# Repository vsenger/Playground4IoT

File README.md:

# Playground4IoT

*"There are three states of being: Not knowing, action and completion"*
Cult of Done Manifesto, Bre Pettis

Welcome Playgrounder to our repository where you can find libraries, firmwares, Arduino Sketch, tutorials and more for Playground4IoT development board. Playground4IoT is a development board that make easy and fun to start playing, prototyping and deploying connected devices projects using AWS Services like AWS IoT Core and Amazon FreeRTOS with security for adults, deployment over-the-air and management of big fleets of devices in production.

This project was done by AWS Developer Relations Team but is open-source, don't hesitate to clone it, produce, have fun, make money, change the world or anything else you dream. Developer Relations Team exist to help you to make it happen, count on us.. ALWAYS!

## Technical Resume

*"Accept that everything is a draft. It helps to get it done."*
The Cult of Done Manifesto, Bre Pettis

This board is based on ESP32, a powerful SoC that can run in low-energy with solar panel and simple battery forever and you can program using Arduino IDE, libraries and frameworks or you can go deeper and programa with Amazon FreeRTOS for industry ready devices.

* Based on ESP32 SoC (System-on-chip) with WIFI and Bluetooth
* Accelerometer Sensor
* Temperature, Humidity and Pressure sensor
* Light sensor
* Battery voltage sensor
* Solar panel sensor
* Groovy connectors
* External Solar Panel Connector
* External Battery Connector
* Battery charger system (cable / solar panel)
* And a lot of love!

## Let's Play!

*"People without dirty hands are wrong, doing something makes you right!"*
The Cult of Done Manifesto, Bre Pettis

Here we have a simple description image showing the main parts:

1. Power on / off
2. IoT Button: you can use as IoT button or anything else!
3. The loooovely OLED display: you can code turn on and off to save energy, sure thing!
4. ESP32: the core! and it's compatible with Amazon FreeRTOS and very cheap
5. GPIO: the place you can extend in a "maker way"
6. Reset Button
7. Solar panel connector: yesss! I can survive with Sun, at least in Brazil ahahah
8. External Battery Connector
9. USB C: you can use to charge the battery (nice!!!), to upload firmware hard-wire (but you can do it over-the-air!) or to debug your board
10. USB to Serial Controller: this is the CH340 chip, you may need or not to install a driver for it
11. You will find three additional connectors under the board and they are Grove compatible, so you can plug [200+ different sensors](https://www.seeedstudio.com/catalogsearch/result/index/?cat=890&q=grove).

To start playing with this device (or toy?!?) we have those main steps:
1. Install Playground4IoT usb driver
1. Install and setup Arduino IDE environment: install Arduino IDE itself and setup for E	SP32 development 
1. Install Arduino libraries for the Playground4IoT sensors
1. Create a thing to represent your board in AWS IoT Core
1. Setup the wifi credential, root-ca, device certificate and private key inside the Arduino C code
1. Upload the Arduino code to your board using an USB cable
1. Open AWS IoT Core console and start playing with your board

Now let's go deep in each step!

## 1. Install Playground4IoT usb driver

Our board uses a chip called CH340 to communicate throught the USB-C port, this chip is actualy a Serial - USB converter so once you have the driver installed you will see the Playground4IoT as a Serial port (windows: COM1, COM7, COMx - linux /dev/acm0 /dev/usb0 - macs /dev/cu.wchusbserial). 

> **_NOTE:_**  MacOS Mojave (and newer) already includes a CH34x driver from Apple. Do not install other versions as it may cause issues. Read more on https://github.com/adrianmihalko/ch340g-ch34g-ch34x-mac-os-x-driver/pull/19.

Follow this nice sparkfun.com tutorial to install the driver: https://learn.sparkfun.com/tutorials/how-to-install-ch340-drivers/all

## 2. Arduino IDE

We have different ways to start programming our Playground4IoT that is based on ESP32 SoC and the simple way to do it is using Arduino IDE. It's a very popular IDE / tool for writing firmwares they call sketches using a simplified C sintax with many libraries to abstract all the hardware and C complex code.

To install Arduino IDE go to Arduino Web Site, download and install it, it's quite simlpe. Here is the link: https://www.arduino.cc/en/Main/Software

After installing the Arduino IDE we must add the ESP32 support. 

1) Open your Arduino IDE

2) Go to File -> Preferences

3) Enter https://dl.espressif.com/dl/package_esp32_index.json into the “Additional Board Manager URLs” field as shown in the figure below. Then, click the “OK” button:

4) Open the Boards Manager. Go to Tools > Board > Boards Manager…

5) Search for ESP32 and press install button for the “ESP32 by Espressif Systems“:

Now wait until it finish the downlaod and install

All done with ESP32 support for Arduino IDE:

6) Choose the "ESP32 Dev Module" in boards manager:

7) Now it's time to find your USB port, don't plug your board in your computer and check which ports you have on the Tools -> Port menu:

8) Now plug your Playground4IoT and check this menu again, you should see something new like here that COM7 is the choosen port:

## 3. Install Arduino Libraries for our Sensors

The Playground for IoT uses some sensors that has specific C libraries to make it easy to use. All we need to do is copy the folders in /Playground4IoT/Arduino/Libraries to your $HOME/Documents/Arduino/Library.

## 4. AWS IoT Core Setup

1) Now we need to setup the cloud side of the moon... We will create a thing to represent our Playground4IoT board and also the certificate and security keys. Open your AWS IoT Core Console and click Manage -> Things -> Register a single AWS IoT thing:

2) Let's choose "Create a single thing"

3) Now give a name to your thing and click next

4) Now choose "One-click certificate creation"

5) You can finally download your thing's certificate and private key

6) Click Activate to make your certicates valid

7) Download ROOT Certificate Authority clicking in "A root CA for AWS IoT Download" (this opens the AWS documentation and you'll need to choose one of the CAs on the page)

8) You will be redirected to another page that you can choose some options:

9) Now we need to take note of our AWS IoT Core endpoint to use in the next step. Open AWS IoT Core Console and click settings

10) We need to create a policy for our device, click Policies -> Create

11) Give a name and choose action iot:* and replace topic name with * (just for testing proposal, the policy for real projects should be restrictive!). Choose Effect Allow and click Create

12) Now let's associate the policy with the Thing Certificate, to do this click in the IoT Thing you've created, click Security and then click in the Certificate:

13) Click Policies

14) Click Actions menu -> Attach Policy

15) Choose the created Policy and click Attach:

Ufff, done!

## 5. Let's code!

1) Clone Playground4IoT repo: git clone https://github.com/vsenger/Playground4IoT

2) Open your Arduino IDE and make sure you selected the right USB port and ESP32 board!

3) Open the Arduino Sketch with current the firmware located inside the folder you clone the github repo: Playground4IoT/arduino/Playground4IoTFirmware-V0/

4) Setup your SSID and password: scroll down to the line around 60 and change:

1. The host name to your AWS IoT Core Thing name
2. SSID and passsword
3. Optional: change the name of the topics we are going to use to communicate with our board 

5) Let's configure our credentials: click in secrets.h tab and then update:

1. AWS IoT Core endpoint
2. ROOT CA certificate: open the downloaded file and copy and paste the content
3. Same things for Device Certificate and Private Key. 

## 6. Upload and fingers crossed

Now click the Upload button and wait until it compile and upload to your board. Keep your eyes in the log message panel, it's "normal" to have warning messages :).

## 7. Let's Play! 

Time to have fun! Open your AWS IoT Core Console and click Test

Type playground/sensors and click Subscribe

Type playground/sensors and click Subscribe

Now you should start seeing the json results!

## 8. Oppss, not working and now?

Chime Vini vsenger@ is now the first option but you can check the following:

1. Is your USB port ok?
2. Did you get any error message during the compile and upload process?
3. Did you choose the right Arduino Board setting to ESP32 Dev?
4. Can you open the Arduino Serial monitor?

## 9. More to come!

From here you can start changing the Arduino code to improve anything you want or do some local logic implementation reacting locally based on sensors data.

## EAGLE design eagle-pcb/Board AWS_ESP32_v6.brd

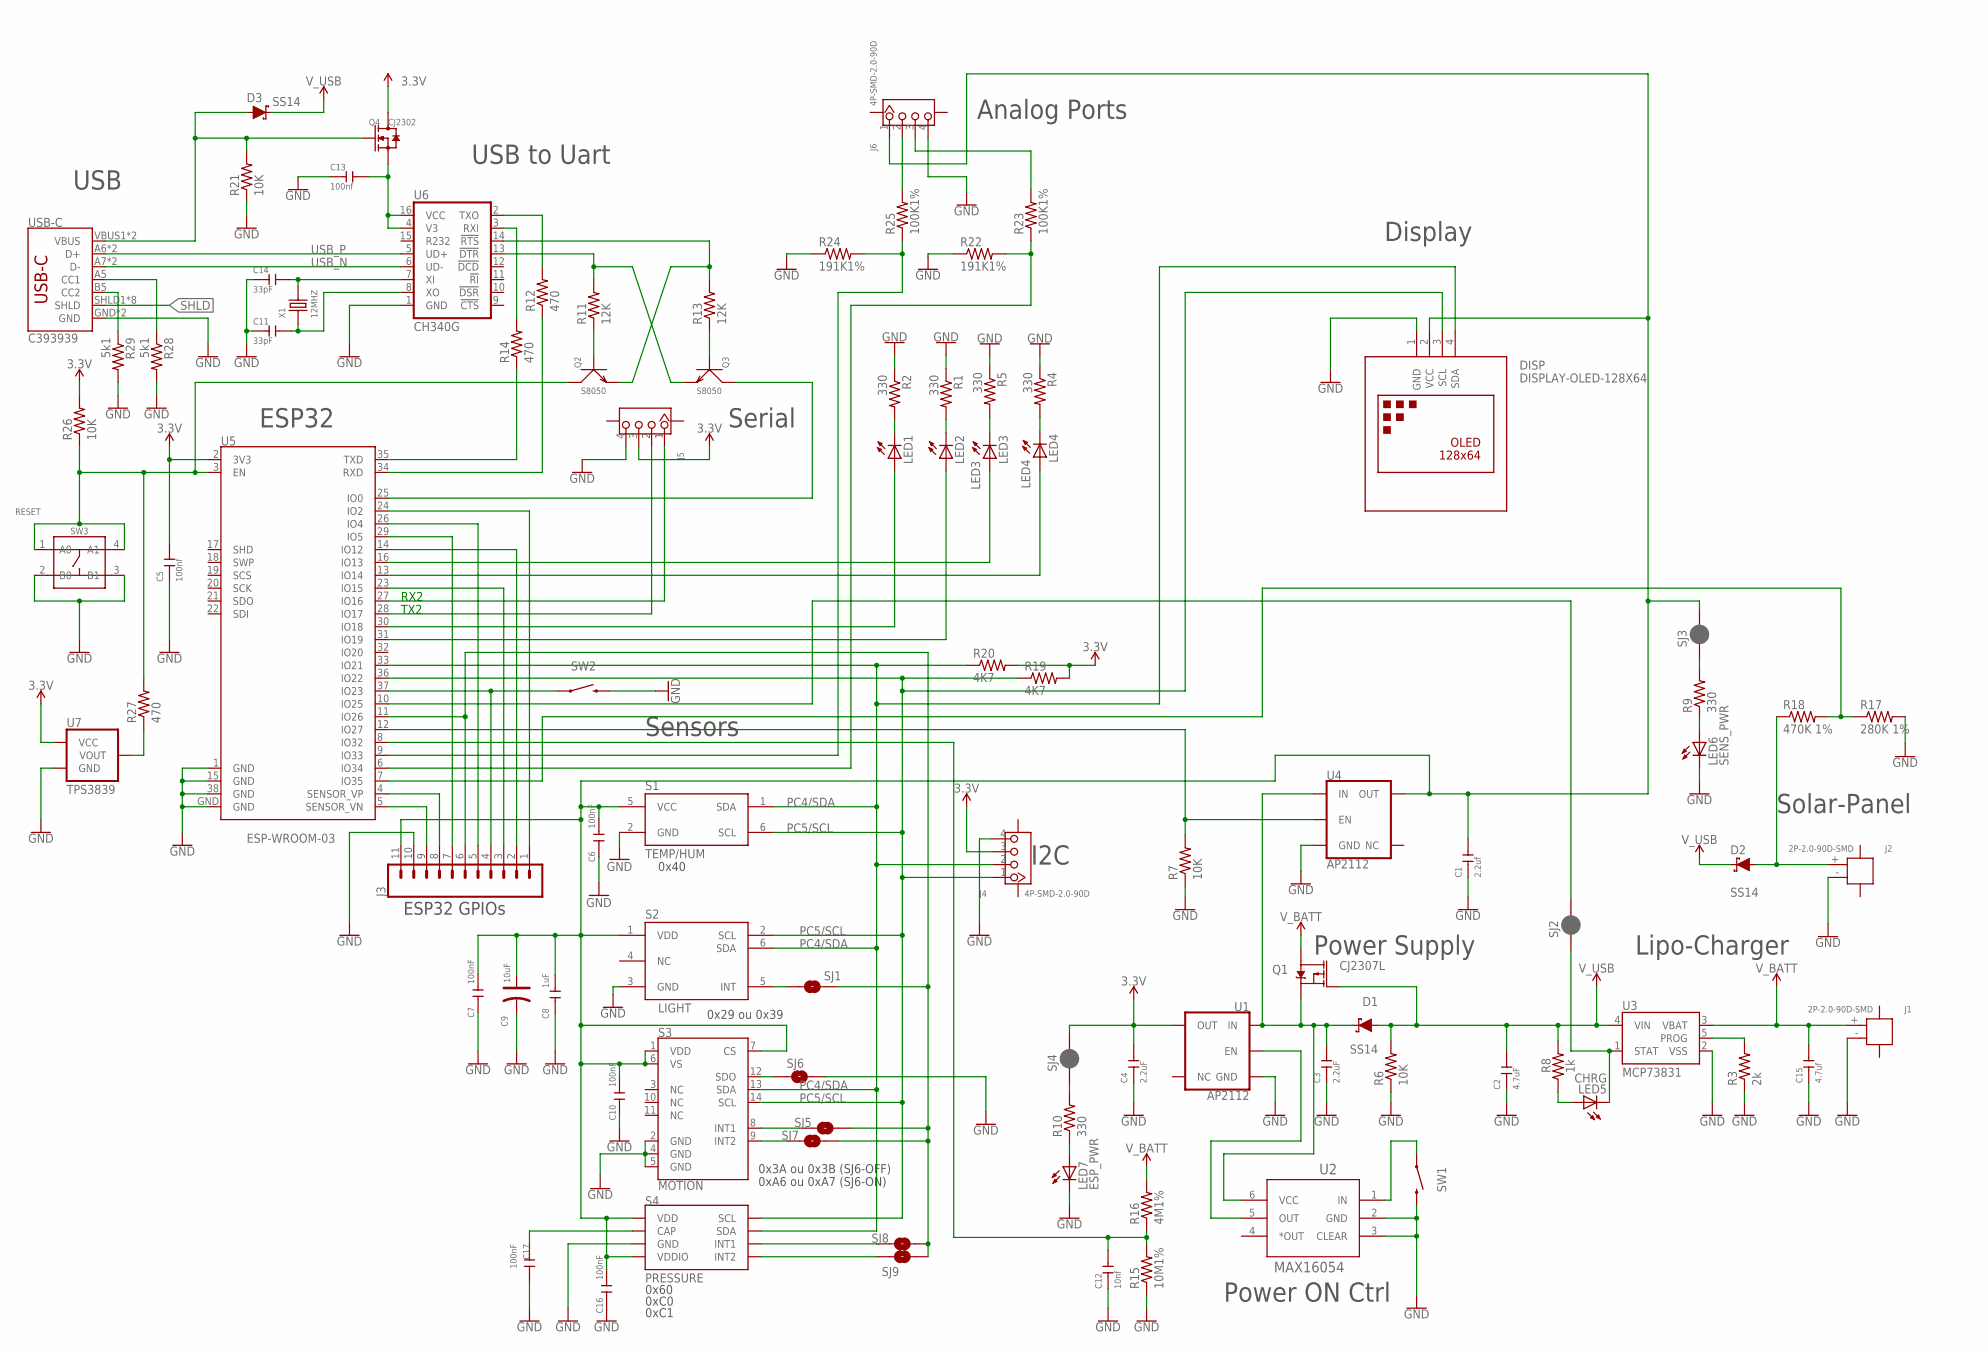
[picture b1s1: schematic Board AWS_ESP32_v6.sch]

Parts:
C1: 2.2uf; C0603
C2: 4.7uF; C0603
C3, C4: 2.2uF; C0603
C5, C13: 100nf; C0603
C6, C7, C10, C16, C17: 100nF; C0603
C8: 1uF; C0805
C9: 10uF; AVX-A
C11, C14: 33pF; C0603
C12: 10nf; C0603
C15: 4.7uf; C0603
D1, D2, D3: SS14; SMA-DIODE
DISP: DISPLAY-OLED-128X64; DISPLAY-OLED-128X64-I2C
J1, J2: 2P-2.0-90D-SMD; HW2-SMD-2.0-90D
J3: CONN_11; 1X11
J4, J5, J6: 4P-SMD-2.0-90D; HW4-SMD-2.0-90D
LED1: LED1; LED-0603
LED2: LED2; LED-0603
LED3: LED3; LED-0603
LED4: LED4; LED-0603
LED5: CHRG; LED-0603
LED6: SENS_PWR; LED-0603
LED7: ESP_PWR; LED-0603
Q1: CJ2307L; SOT23-3
Q2, Q3: S8050; SOT-23
Q4: CJ2302; SOT-23
R1, R2, R4, R5, R9, R10: 330; 0805
R3: 2k; 0805
R6, R7, R21, R26: 10K; 0805
R8: 1k; 0805
R11, R13: 12K; 0805
R12, R14, R27: 470; 0805
R15: 10M1%; 0805
R16: 4M1%; 0805
R17: 280K 1%; 0805
R18: 470K 1%; 0805
R19, R20: 4K7; 0805
R22, R24: 191K1%; 0805
R23, R25: 100K1%; 0805
R28, R29: 5k1; 0805
S1: TEMP/HUM; WSON6
S2: LIGHT; FN-6
S3: MOTION; LGA-14
S4: PRESSURE; LGA8
SJ1: IRQ_LIGHT; SJ_2S-NO
SJ2, SJ3, SJ4: JUMPER-SMT_2_NC_PASTE_SILK; SMT-JUMPER_2_NC_PASTE_SILK
SJ5, SJ7, SJ8: INT1; SJ_2S-NO
SJ6: ADXL_ADDRESS; SJ_2S-NO
SJ9: INT2; SJ_2S-NO
SW1, SW2: MOMENTARY-SWITCH-SPST-SMD-6.0X3.5MM; TACTILE_SWITCH_SMD_6.0X3.5MM
SW3: RESET; SW4-SMD-6.0X6.0X5.0MM
U1, U4: AP2112; SOT23-5
U2: MAX16054; SOT23-6
U3: MCP73831; SOT23-5
U5: ESP-WROOM-03
U6: CH340G; SO016
U7: TPS3839; SOT23-3
USB-C: C393939; SPARKFUN-CONNECTORS_USB-C-16P
X1: 12MHZ; X2-SMD-5.0X3.2X1.3MM

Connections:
3.3V: C4.2, C5.2, J4.3, J5.3, Q4.3 (D), R19.2, R20.2, R26.2, SJ4.2, U1.5 (OUT), U5.2 (3V3), U7.3 (VCC)
BEE_RESET: Q2.3 (C), R26.1, R27.2, SW3.1 (A0), SW3.4 (A1), U5.3 (EN)
GND: C1.1, C2.1, C3.1, C4.1, C5.1, C6.1, C7.1, C8.2, C9.-, C10.1, C11.1, C12.1, C13.1, C14.1, C15.1, C16.1, C17.2, DISP.1 (GND), J1.- (2), J2.- (2), J3.10, J4.4, J5.4, J6.4, LED6.C, LED7.C, R1.1, R2.1, R3.1, R4.1, R5.1, R6.1, R7.1, R15.1, R17.2, R21.1, R22.1, R24.1, R28.2, R29.2, S1.2 (GND), S2.3 (GND), S3.2 (GND), S3.4 (GND), S3.5 (GND), S4.3 (GND), SJ6.2, SW1.2, SW2.2, SW3.2 (B0), SW3.3 (B1), U1.2 (GND), U2.2 (GND), U2.3 (CLEAR), U3.2 (VSS), U4.2 (GND), U5.1 (GND), U5.15 (GND), U5.38 (GND), U5.GND, U6.1 (GND), U7.1 (GND), USB-C.GND, USB-C.GND2 (GND)
unnamed: C1.2, C6.2, C7.2, C8.1, C9.+, C10.2, C16.2, DISP.2 (VCC), J3.11, J6.1, S1.5 (VCC), S2.1 (VDD), S3.1 (VDD), S3.6 (VS), S3.7 (CS), S4.1 (VDD), S4.4 (VDDIO), SJ3.2, U4.5 (OUT)
unnamed: LED3.A, U5.16 (IO13)
unnamed: D2.A, J2.+ (1), R18.1
unnamed: R27.1, U7.2 (VOUT)
unnamed: LED1.A, U5.30 (IO18)
unnamed: J3.5, U5.26 (IO4)
unnamed: C17.1, S4.2 (CAP)
unnamed: S3.8 (INT1), SJ5.1
unnamed: S3.9 (INT2), SJ7.1
unnamed: C13.2, Q4.2 (S), U6.4 (V3), U6.16 (VCC)
unnamed: LED2.A, U5.31 (IO19)
unnamed: C12.2, R15.2, R16.1, U5.8 (IO32)
unnamed: J3.4, SW2.1, U5.37 (IO23)
unnamed: SW1.1, U2.1 (IN)
unnamed: C14.2, U6.7 (XI), X1.2
unnamed: J5.1, U5.27 (IO16)
unnamed: J5.2, U5.28 (IO17)
unnamed: U1.3 (EN), U2.5 (OUT)
unnamed: Q2.1 (B), R11.1
unnamed: C11.2, U6.8 (XO), X1.1
unnamed: S3.12 (SDO), SJ6.1
unnamed: R3.2, U3.5 (PROG)
unnamed: D3.A, Q4.1 (G), R21.2, USB-C.VBUS1 (VBUS), USB-C.VBUS2 (VBUS)
unnamed: R29.1, USB-C.B5 (CC2)
unnamed: S4.6 (INT1), SJ8.1
unnamed: S4.5 (INT2), SJ9.1
unnamed: S2.5 (INT), SJ1.1
unnamed: R12.1, U5.34 (RXD)
unnamed: R14.1, U5.35 (TXD)
unnamed: Q3.1 (B), R13.1
unnamed: R28.1, USB-C.A5 (CC1)
unnamed: LED1.C, R2.2
unnamed: LED2.C, R1.2
unnamed: Q2.2 (E), R13.2, U6.14 (!RTS)
unnamed: LED4.C, R4.2
unnamed: LED3.C, R5.2
unnamed: Q3.3 (C), U5.25 (IO0)
unnamed: Q3.2 (E), R11.2, U6.13 (!DTR)
unnamed: R24.2, R25.1, U5.9 (IO33)
unnamed: R22.2, R23.1, U5.6 (IO34)
unnamed: J6.2, R25.2
unnamed: J6.3, R23.2
unnamed: R17.1, R18.2, U5.7 (IO35)
unnamed: R14.2, U6.3 (RXI)
unnamed: R12.2, U6.2 (TXO)
unnamed: SJ2.2, U5.10 (IO25)
unnamed: J3.7, U5.29 (IO5)
unnamed: LED5.A, R8.1
unnamed: C3.2, D1.C, Q1.2 (S), U1.1 (IN), U2.6 (VCC), U4.1 (IN)
unnamed: LED7.A, R10.1
unnamed: R10.2, SJ4.1
unnamed: LED5.C, SJ2.1, U3.1 (STAT)
unnamed: LED4.A, U5.13 (IO14)
unnamed: LED6.A, R9.1
unnamed: R7.2, U4.3 (EN), U5.12 (IO27)
unnamed: R9.2, SJ3.1
unnamed: J3.9, U5.5 (SENSOR_VN)
unnamed: J3.8, U5.4 (SENSOR_VP)
unnamed: J3.3, U5.23 (IO15)
unnamed: J3.2, U5.14 (IO12)
unnamed: J3.1, U5.24 (IO2)
PC4/SDA: DISP.4 (SDA), J4.2, R20.1, S1.1 (SDA), S2.6 (SDA), S3.13 (SDA), S4.7 (SDA), U5.33 (IO21)
PC5/SCL: DISP.3 (SCL), J4.1, R19.1, S1.6 (SCL), S2.2 (SCL), S3.14 (SCL), S4.8 (SCL), U5.36 (IO22)
PD3/IRQ: J3.6, SJ1.2, SJ5.2, SJ7.2, SJ8.2, SJ9.2, U5.11 (IO26)
SHLD: USB-C.SHLD1 (SHLD), USB-C.SHLD2 (SHLD), USB-C.SHLD3 (SHLD), USB-C.SHLD4 (SHLD), USB-C.SHLD5 (SHLD), USB-C.SHLD6 (SHLD), USB-C.SHLD7 (SHLD), USB-C.SHLD8 (SHLD)
USB_N: U6.6 (UD-), USB-C.A7 (D-), USB-C.B7 (D-)
USB_P: U6.5 (UD+), USB-C.A6 (D+), USB-C.B6 (D+)
V_BATT: C15.2, J1.+ (1), Q1.3 (D), R16.2, U3.3 (VBAT)
V_USB: C2.2, D1.A, D2.C, D3.C, Q1.1 (G), R6.2, R8.2, U3.4 (VIN)

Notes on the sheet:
USB
I2C
Sensors
0x60
0xC1
0xC0
0x29 ou 0x39
0x40
Serial
ESP32
Power Supply
USB to Uart
Analog Ports
Lipo-Charger
ESP32 GPIOs
RX2
TX2
Solar-Panel
Display
0x3A ou 0x3B (SJ6-OFF)
0xA6 ou 0xA7 (SJ6-ON)
Power ON Ctrl

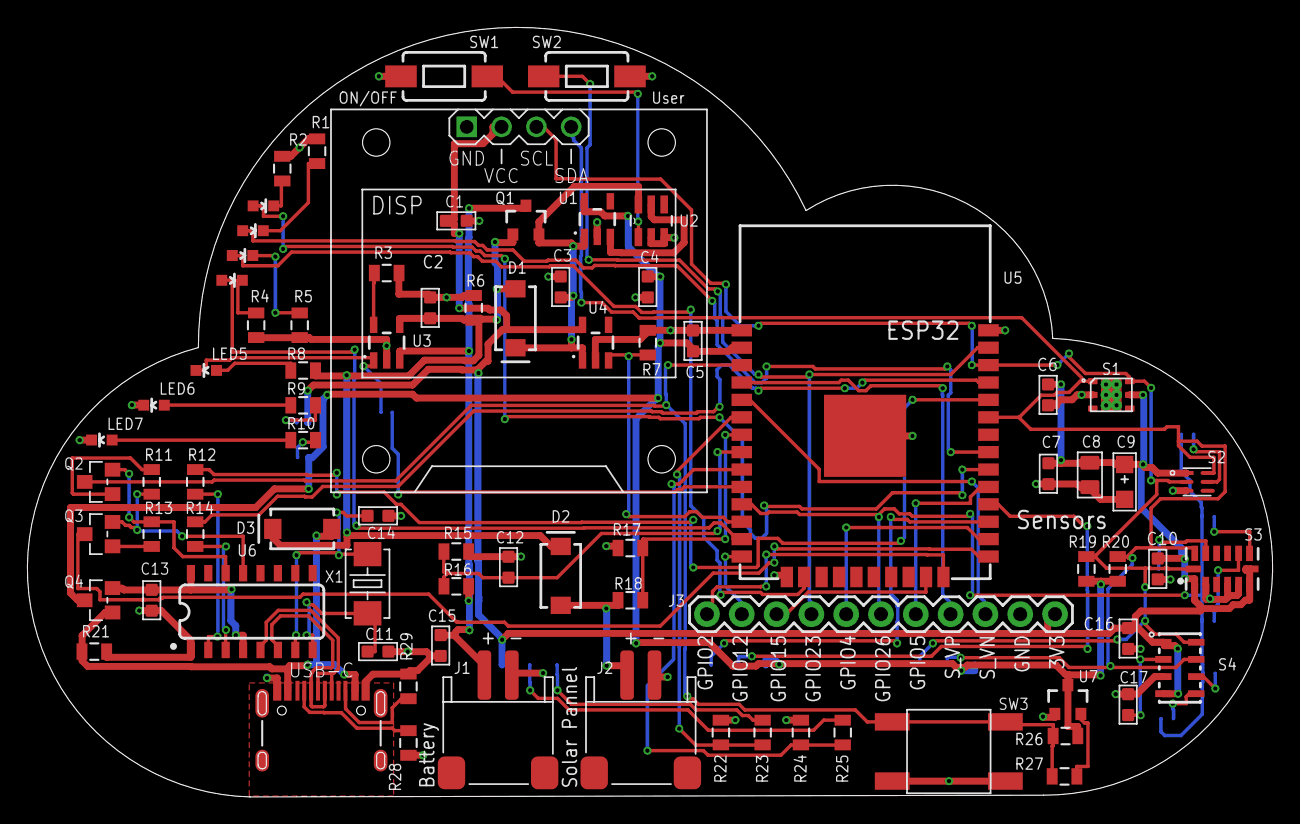
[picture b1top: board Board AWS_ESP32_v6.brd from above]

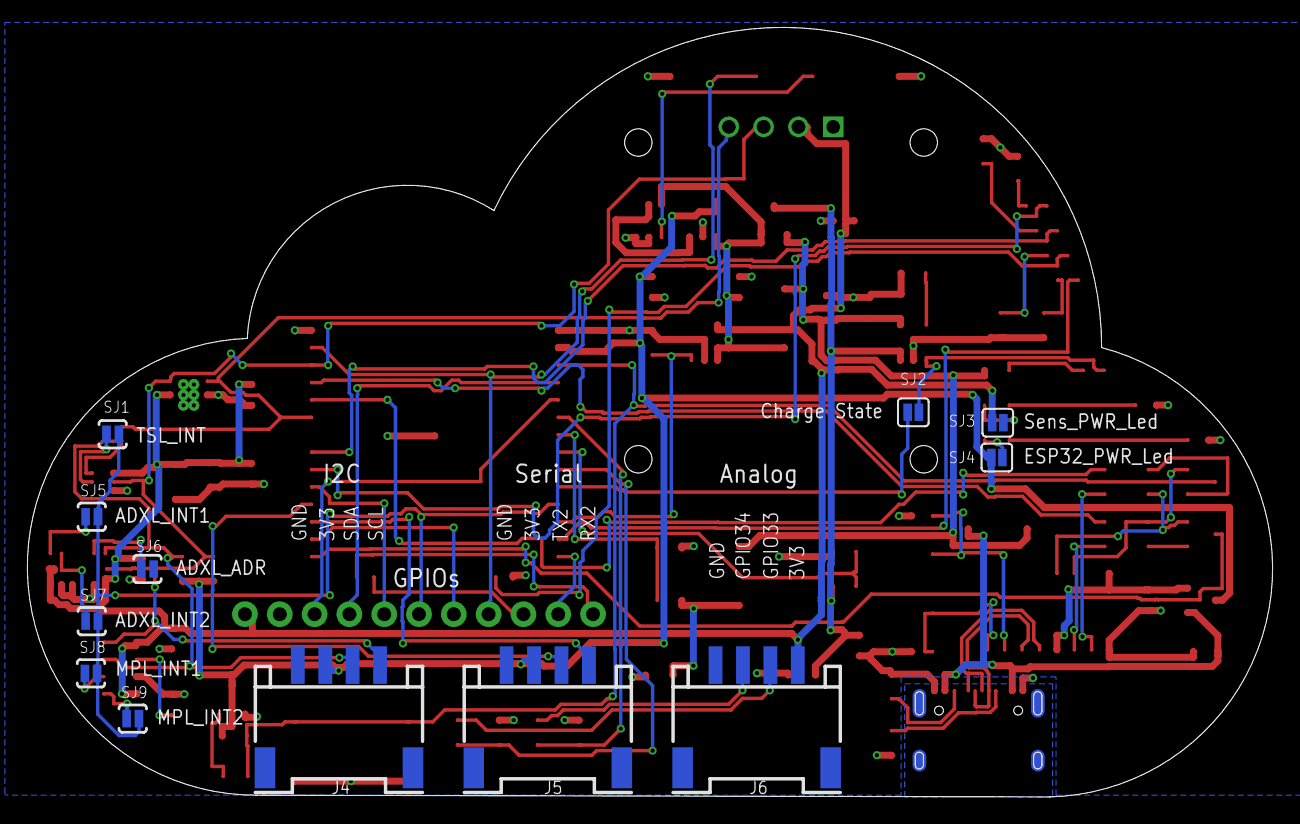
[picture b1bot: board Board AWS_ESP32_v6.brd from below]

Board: 2 copper layers, 90.8 x 56.1 mm, 92 parts (12 on the bottom side), 72 nets.

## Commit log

2020-09-10 readme
2020-09-21 tutorial
2020-10-12 missed images
2020-10-12 more missed content
2020-10-13 adds missing libraries ArduinoJson and arduino-mqtt
2020-10-13 adds CH34x Mojave+ warning on README
2020-10-15 Update README.md
    Fix a bug!
2020-10-15 Update README.md
    Fix a typo and add some important info.
2020-10-19 case 3d
2021-04-23 Add .DS_Store to gitignore
2021-04-23 Remove .DS_Store files

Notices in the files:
parts and their libraries:
SparkFun-Sensors: Licensing: Creative Commons ShareAlike 4.0 International - https://creativecommons.org/licenses/by-sa/4.0
diy-modules: Released under the Creative Commons Attribution 4.0 International License: http://creativecommons.org/licenses/by/4.0
